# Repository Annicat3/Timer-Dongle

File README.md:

# Timer-Dongle

## What is it?
This project is a small USB timer based on the CH552G microcontroller. It has 6 LEDs, a piezo buzzer and 2 buttons.  
The time can be selected in 10-minute steps, from 10 to 60 minutes. The LEDs show the selected time ans later show the progress of the timer. 
When the Timer finishes, the LEDs blink and the buzzer makes a sound.  

## Why did I make it?
I wanted to make something useful that I could actually use while working or studying. I also thought it would be fun to turn a simple electronic project into something with personality.  
Instead of using a normal rectangular PCB, I designed mine in the shape of a cat. I also added a small cat face and other details to the silkscreen.  

## How does it work?
1. Plug the timer into a USB port.
2. Press the time button to choose a time from 10 to 60 minutes.
3. Press the start button to start the timer.
4. The six LEDs slowly turn off as the timer runs.
5. When the timer reaches zero, the LEDs blink and the buzzer sounds.
6. Press the time button to stop the alarm and choose a new time.

## PCB  
I designed the schematic and PCB in KiCad.  

### Schematic

### 3D View

## Firmware
The Firmware is written for the CH552G using CH55xduino. 

## CAD
I also experimented with designing a simple case for the PCB in Onshape.  
[Onshape link](https://cad.onshape.com/documents/177762d436c217a9aff06dc5/w/83f6144ef2d4be5b708dd7f0/e/6c6f59c3ce17ec4403d9fee3?renderMode=0&uiState=6a90b07a0fc47dc81437df1d)  

## Bill of Materials (BOM)
|Item    |  Qty | Cost | Link |
|--------|------|------|------|
|PCB | 5 | $22.14 | [Gerber files](PCB/Timer-Dongle.gerbers.zip) |
| 3D printed case | 1 | $0.00 | [Stl File](CAD/Timer.Dongle.stl) |
|WCH CH552G Microcontroller | 1 | $0.75 | [LCSC C111292](https://www.lcsc.com/product-detail/Microcontrollers-MCU-MPU-SOC_WCH-Jiangsu-Qin-Heng-CH552G_C111292.html)|
| Murata GRM188R72A104KA35D, 100nF, 0603 | 2 | $0.18 | [LCSC C77058](https://www.lcsc.com/product-detail/C77058.html) |
| YAGEO RT0603BRD07470RL, 470Ω, 0603 | 6 | $0.55 | [LCSC C705779](https://www.lcsc.com/product-detail/C705779.html) |
| Panasonic ERA3AEB103V, 10kΩ, 0603 | 1 | $0.53 | [LCSC C190610](https://www.lcsc.com/product-detail/C190610.html) |
| XUNPU TS-1088-AC02016 tactile switch | 3 | $0.69 | [LCSC C720475](https://www.lcsc.com/product-detail/C720475.html) |
| Murata PKMCS0909E4000-R1 Piezo Buzzer | 1 | $1.02 | [LCSC C910763](https://lcsc.com/product-detail/Buzzers_Murata-Electronics-PKMCS0909E4000-R1_C910763.html) | 
| 0805 SMD LEDs | 6 | $2.43 | [LCSC C5879058](https://www.lcsc.com/product-detail/C5879058.html) |
| Shipping |  | $12,79 | |
| Total |     | $41.08 | |

## Hack Club Dongle YSWS
This project was created as part of Hack Club's YSWS program, [Dongle](https://dongle.hackclub.com). It was my first time designing a PCB and I learned a lot about schematics, PCB design, routing, and choosing components along the way.

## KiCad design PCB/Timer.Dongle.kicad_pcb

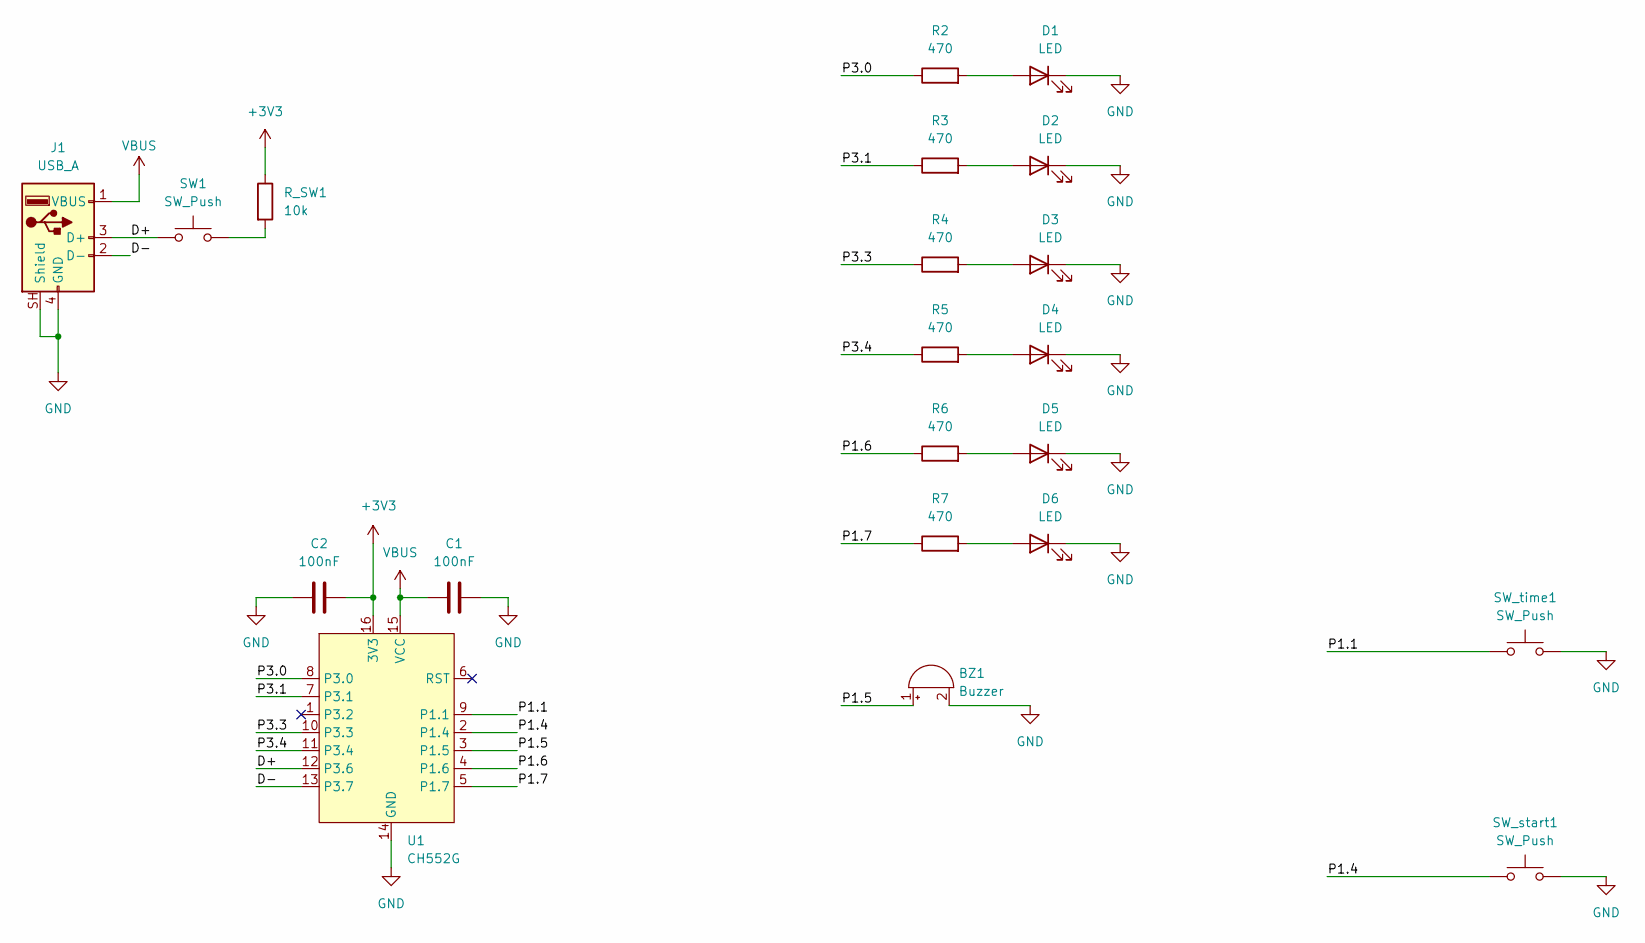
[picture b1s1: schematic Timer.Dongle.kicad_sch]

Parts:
BZ1: Buzzer; Buzzer_Murata_PKMCS0909E
C1, C2: 100nF; C_0603_1608Metric
D1, D2, D3, D4, D5, D6: LED; LED_0805_2012Metric
J1: USB_A; USB-A
R2, R3, R4, R5, R6, R7: 470; R_0603_1608Metric
R_SW1: 10k; R_0603_1608Metric
SW1: SW_Push; SW_SPST_TS-1088-xR020
SW_start1: SW_Push; SW_SPST_TS-1088-xR020
SW_time1: SW_Push; SW_SPST_TS-1088-xR020
U1: CH552G; JEITA_SOIC-16_3.9x9.9mm_P1.27mm

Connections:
+3V3: C2.1, R_SW1.1, U1.16 (3V3)
/D+: J1.3 (D+), SW1.1, U1.12 (P3.6)
/D-: J1.2 (D-), U1.13 (P3.7)
/P1.1: SW_time1.1, U1.9 (P1.1)
/P1.4: SW_start1.1, U1.2 (P1.4)
/P1.5: BZ1.1 (+), U1.3 (P1.5)
/P1.6: R6.1, U1.4 (P1.6)
/P1.7: R7.1, U1.5 (P1.7)
/P3.0: R2.1, U1.8 (P3.0)
/P3.1: R3.1, U1.7 (P3.1)
/P3.3: R4.1, U1.10 (P3.3)
/P3.4: R5.1, U1.11 (P3.4)
GND: BZ1.2 (-), C1.1, C2.2, D1.1 (K), D2.1 (K), D3.1 (K), D4.1 (K), D5.1 (K), D6.1 (K), J1.4 (GND), J1.SH (Shield), SW_start1.2, SW_time1.2, U1.14 (GND)
unnamed: D1.2 (A), R2.2
unnamed: D2.2 (A), R3.2
unnamed: D3.2 (A), R4.2
unnamed: D4.2 (A), R5.2
unnamed: D5.2 (A), R6.2
unnamed: D6.2 (A), R7.2
unnamed: R_SW1.2, SW1.2
VBUS: C1.2, J1.1 (VBUS), U1.15 (VCC)

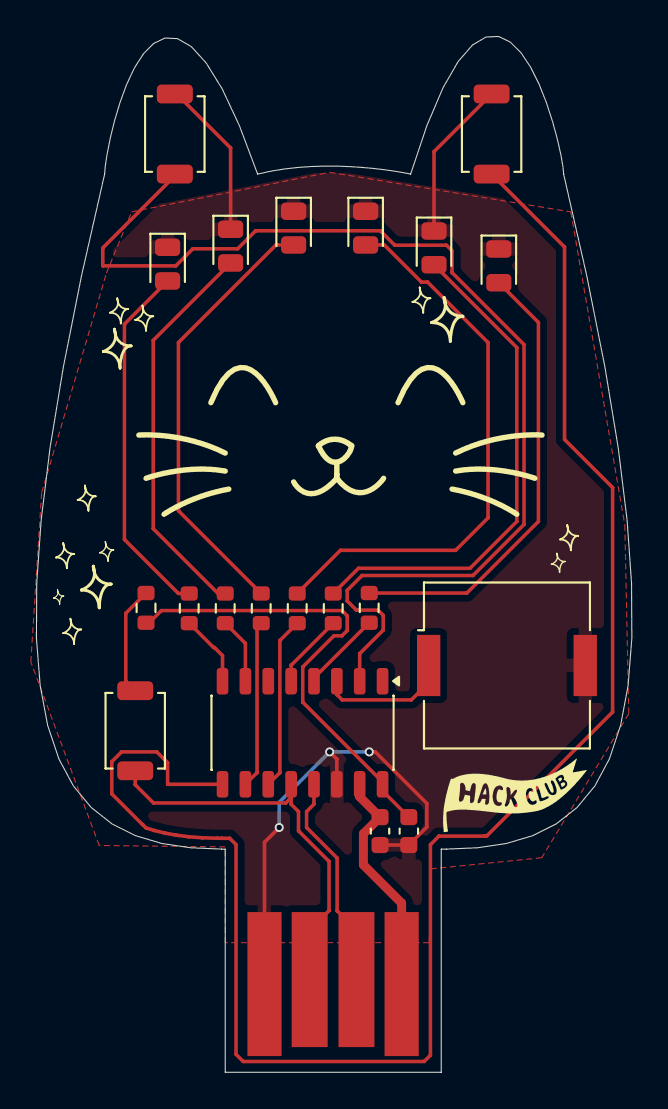
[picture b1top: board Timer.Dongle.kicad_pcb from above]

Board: 2 copper layers, 33.1 x 57.5 mm, 21 parts (0 on the bottom side), 21 nets.
